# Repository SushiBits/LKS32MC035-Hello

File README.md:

# LKS32MD035-Hello

This project implements a simple sensorless six-step commutation BLDC
controller based on the Linko LKS32MC035DL6S8B microcontroller.

Likely the first ever LKS32MD03x project written without vendor library.

## Hardware

See [here](hardware/) for the KiCad project. See schematics
[here](doc/minispin.pdf).

## Firmware

This project is a self-contained Visual Studio Code workspace. Due to my heavy
customization of vendor SDK files, I am not involving PlatformIO.

## Copyright

Copyright &copy; 2026 HIKARU Infotech Shanghai Ltd. All rights reserved.

This is [open-source](LICENSE.md) hardware and software under 3-clause BSD
license.

The `doc/LKS32MC03x*.pdf` and `platform/share/LKS32MC03x.svd` files' copyright
belong to Linko Semiconductor Co. Ltd. with my edits.

Files under `cmsis` copyright Arm Inc. See [its own license](cmsis/LICENSE).

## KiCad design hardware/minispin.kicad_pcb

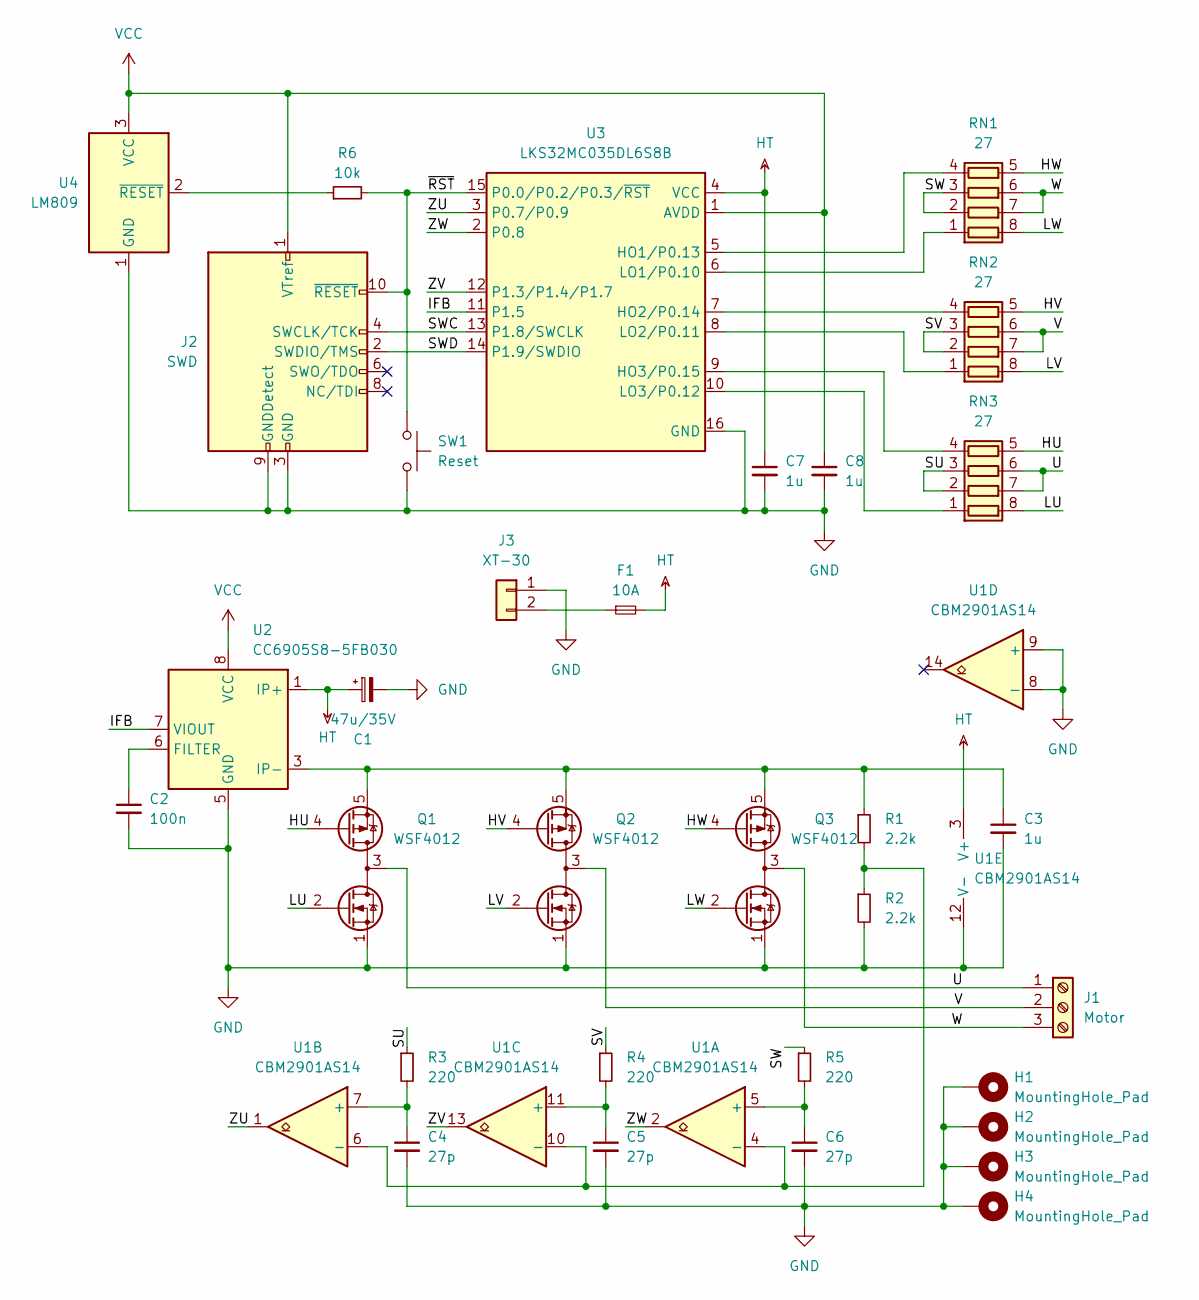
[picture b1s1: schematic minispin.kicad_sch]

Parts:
C1: 47u/35V; CP_EIA-7132-28_AVX-C
C2: 100n; C_0603_1608Metric_Pad1.08x0.95mm_HandSolder
C3, C7, C8: 1u; C_0603_1608Metric_Pad1.08x0.95mm_HandSolder
C4, C5, C6: 27p; C_0603_1608Metric_Pad1.08x0.95mm_HandSolder
F1: 10A; Fuseholder_Cylinder-5x20mm_Stelvio-Kontek_PTF78_Horizontal_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
H1, H2, H3, H4: MountingHole_Pad; MountingHole_3.2mm_M3_Pad_Via
J1: Motor; TerminalBlock_bornier-3_P5.08mm
J2: SWD; PinHeader_2x05_P1.27mm_Vertical
J3: XT-30; AMASS_XT30PW-M_1x02_P2.50mm_Horizontal
Q1, Q2, Q3: WSF4012; TO-252-4
R1, R2: 2.2k; R_0603_1608Metric_Pad0.98x0.95mm_HandSolder
R3, R4, R5: 220; R_0603_1608Metric_Pad0.98x0.95mm_HandSolder
R6: 10k; R_0603_1608Metric_Pad0.98x0.95mm_HandSolder
RN1, RN2, RN3: 27; R_Array_Convex_4x0603
SW1: Reset; SW_SPST_EVQP2
U1: CBM2901AS14; SOIC-14_3.9x8.7mm_P1.27mm
U2: CC6905S8-5FB030; SOIC-8_3.9x4.9mm_P1.27mm
U3: LKS32MC035DL6S8B; SO-16_3.9x9.9mm_P1.27mm
U4: LM809; SOT-23

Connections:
/HU: Q1.4 (G1), RN3.5 (R4.2)
/HV: Q2.4 (G1), RN2.5 (R4.2)
/HW: Q3.4 (G1), RN1.5 (R4.2)
/IFB: U2.7 (VIOUT), U3.11 (P1.5)
/LU: Q1.2 (G2), RN3.8 (R1.2)
/LV: Q2.2 (G2), RN2.8 (R1.2)
/LW: Q3.2 (G2), RN1.8 (R1.2)
/SU: R3.1, RN3.2 (R2.1), RN3.3 (R3.1)
/SV: R4.1, RN2.2 (R2.1), RN2.3 (R3.1)
/SW: R5.1, RN1.2 (R2.1), RN1.3 (R3.1)
/SWC: J2.4 (SWCLK/TCK), U3.13 (P1.8/SWCLK)
/SWD: J2.2 (SWDIO/TMS), U3.14 (P1.9/SWDIO)
/U: J1.1, Q1.3 (S1/D2), RN3.6 (R3.2), RN3.7 (R2.2)
/V: J1.2, Q2.3 (S1/D2), RN2.6 (R3.2), RN2.7 (R2.2)
/W: J1.3, Q3.3 (S1/D2), RN1.6 (R3.2), RN1.7 (R2.2)
/ZU: U1.1, U3.3 (P0.7/P0.9)
/ZV: U1.13, U3.12 (P1.3/P1.4/P1.7)
/ZW: U1.2, U3.2 (P0.8)
/~RST: J2.10 (~RESET), R6.2, SW1.1, U3.15 (P0.0/P0.2/P0.3/~RST)
GND: C1.2, C2.2, C3.2, C4.2, C5.2, C6.2, C7.2, C8.2, H1.1, H2.1, H3.1, H4.1, J2.3 (GND), J2.5 (GND), J2.9 (GNDDetect), J3.1, Q1.1 (S2), Q2.1 (S2), Q3.1 (S2), R2.2, SW1.2, U1.8 (-), U1.9 (+), U1.12 (V-), U2.5 (GND), U3.16 (GND), U4.1 (GND)
HT: C1.1, C7.1, F1.2, U1.3 (V+), U2.1 (IP+), U2.2 (IP+), U3.4 (VCC)
unnamed: F1.1, J3.2
unnamed: C3.1, Q1.5 (D1), Q2.5 (D1), Q3.5 (D1), R1.1, U2.3 (IP-), U2.4 (IP-)
unnamed: RN1.1 (R1.1), U3.6 (LO1/P0.10)
unnamed: RN1.4 (R4.1), U3.5 (HO1/P0.13)
unnamed: RN2.1 (R1.1), U3.8 (LO2/P0.11)
unnamed: RN2.4 (R4.1), U3.7 (HO2/P0.14)
unnamed: RN3.1 (R1.1), U3.10 (LO3/P0.12)
unnamed: RN3.4 (R4.1), U3.9 (HO3/P0.15)
unnamed: C6.1, R5.2, U1.5 (+)
unnamed: R1.2, R2.1, U1.4 (-), U1.6 (-), U1.10 (-)
unnamed: C4.1, R3.2, U1.7 (+)
unnamed: C5.1, R4.2, U1.11 (+)
unnamed: C2.1, U2.6 (FILTER)
unnamed: R6.1, U4.2 (~RESET)
VCC: C8.1, J2.1 (VTref), U2.8 (VCC), U3.1 (AVDD), U4.3 (VCC)

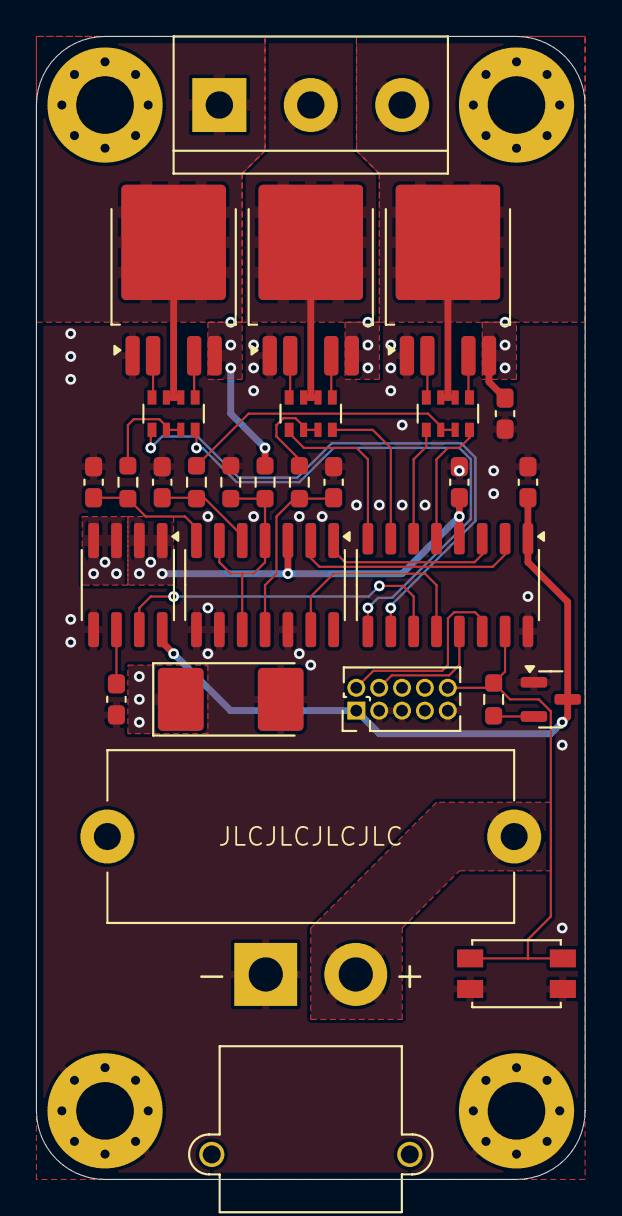
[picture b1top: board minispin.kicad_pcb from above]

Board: 2 copper layers, 30.5 x 63.5 mm, 33 parts (0 on the bottom side), 36 nets.
